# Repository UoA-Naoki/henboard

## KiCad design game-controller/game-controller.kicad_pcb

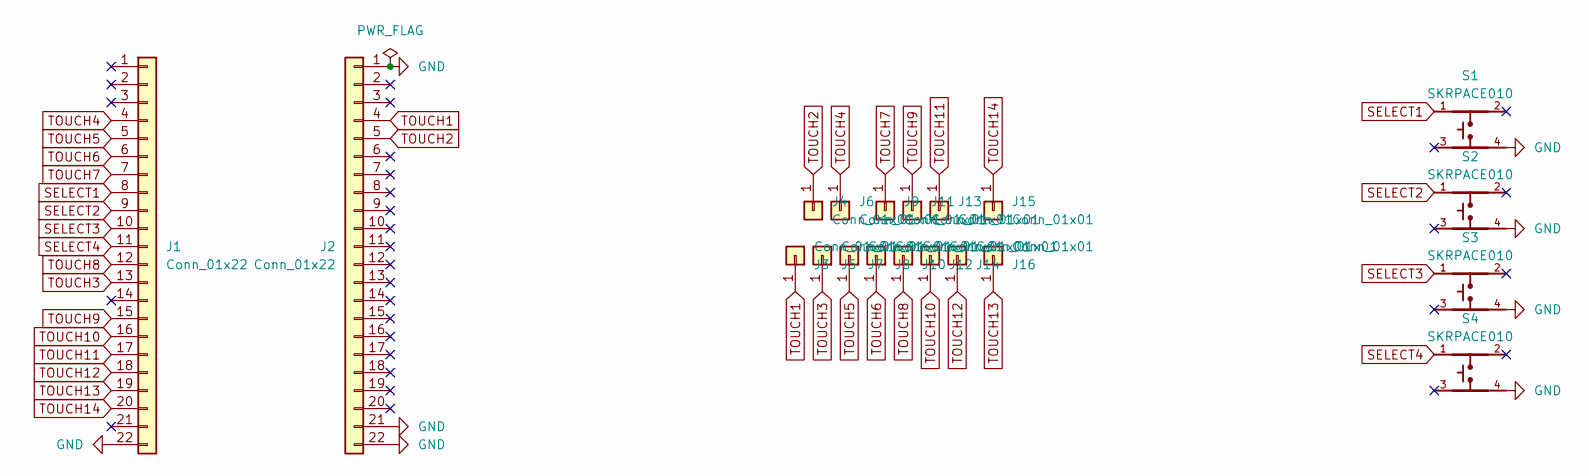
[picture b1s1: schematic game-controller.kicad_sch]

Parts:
J1, J2: Conn_01x22; PinHeader_1x22_P2.54mm_Vertical
J3, J4, J5, J6, J7, J8, J9, J10, J11, J12, J13, J14, J15, J16: Conn_01x01; Pad-CapacitiveTouch
S1, S2, S3, S4: SKRPACE010

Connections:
GND: J1.22, J2.1, J2.21, J2.22, S1.4, S2.4, S3.4, S4.4
SELECT1: J1.8, S1.1
SELECT2: J1.9, S2.1
SELECT3: J1.10, S3.1
SELECT4: J1.11, S4.1
TOUCH1: J2.4, J3.1
TOUCH2: J2.5, J4.1
TOUCH3: J1.13, J5.1
TOUCH4: J1.4, J6.1
TOUCH5: J1.5, J7.1
TOUCH6: J1.6, J8.1
TOUCH7: J1.7, J9.1
TOUCH8: J1.12, J10.1
TOUCH9: J1.15, J11.1
TOUCH10: J1.16, J12.1
TOUCH11: J1.17, J13.1
TOUCH12: J1.18, J14.1
TOUCH13: J1.19, J16.1
TOUCH14: J1.20, J15.1

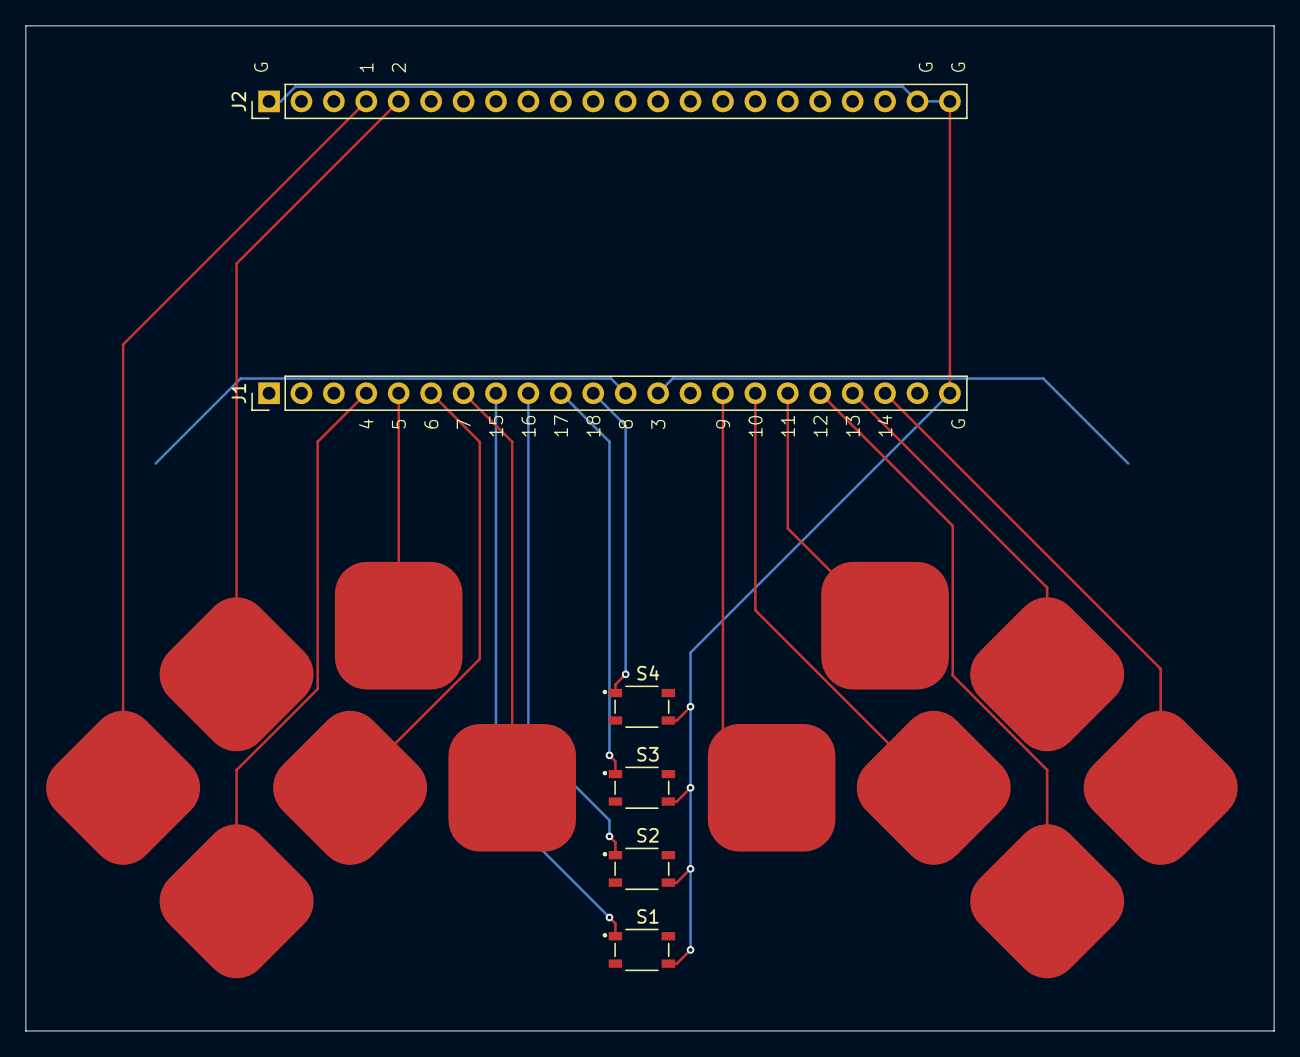
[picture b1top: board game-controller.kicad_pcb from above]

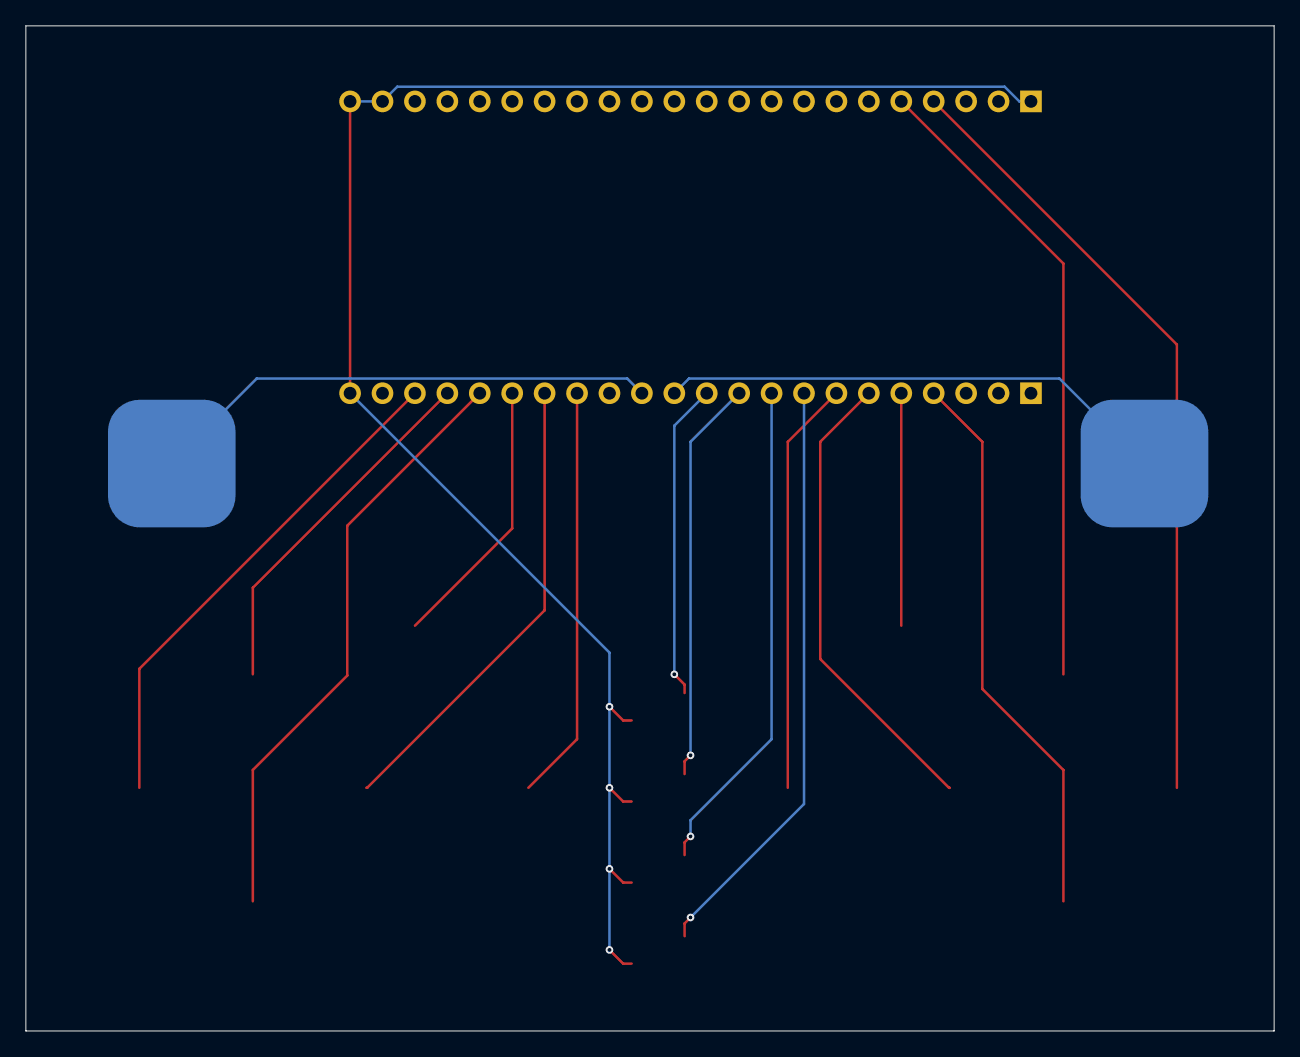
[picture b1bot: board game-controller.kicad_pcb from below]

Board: 2 copper layers, 97.8 x 78.7 mm, 20 parts (2 on the bottom side), 19 nets.

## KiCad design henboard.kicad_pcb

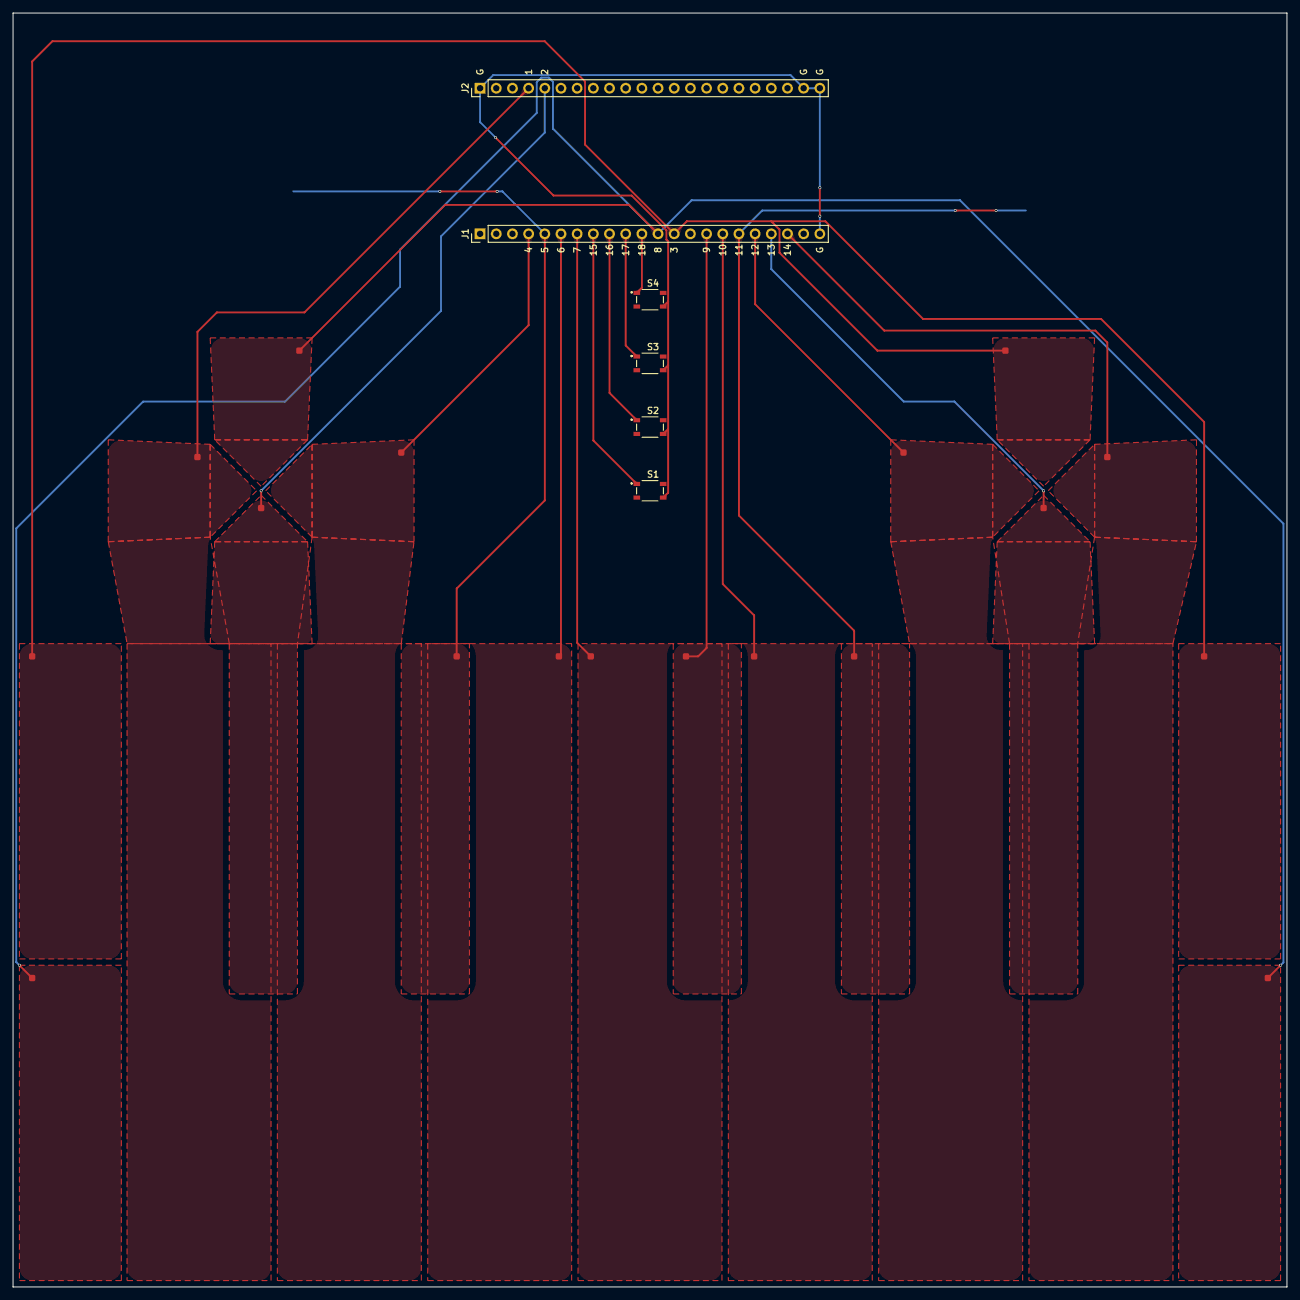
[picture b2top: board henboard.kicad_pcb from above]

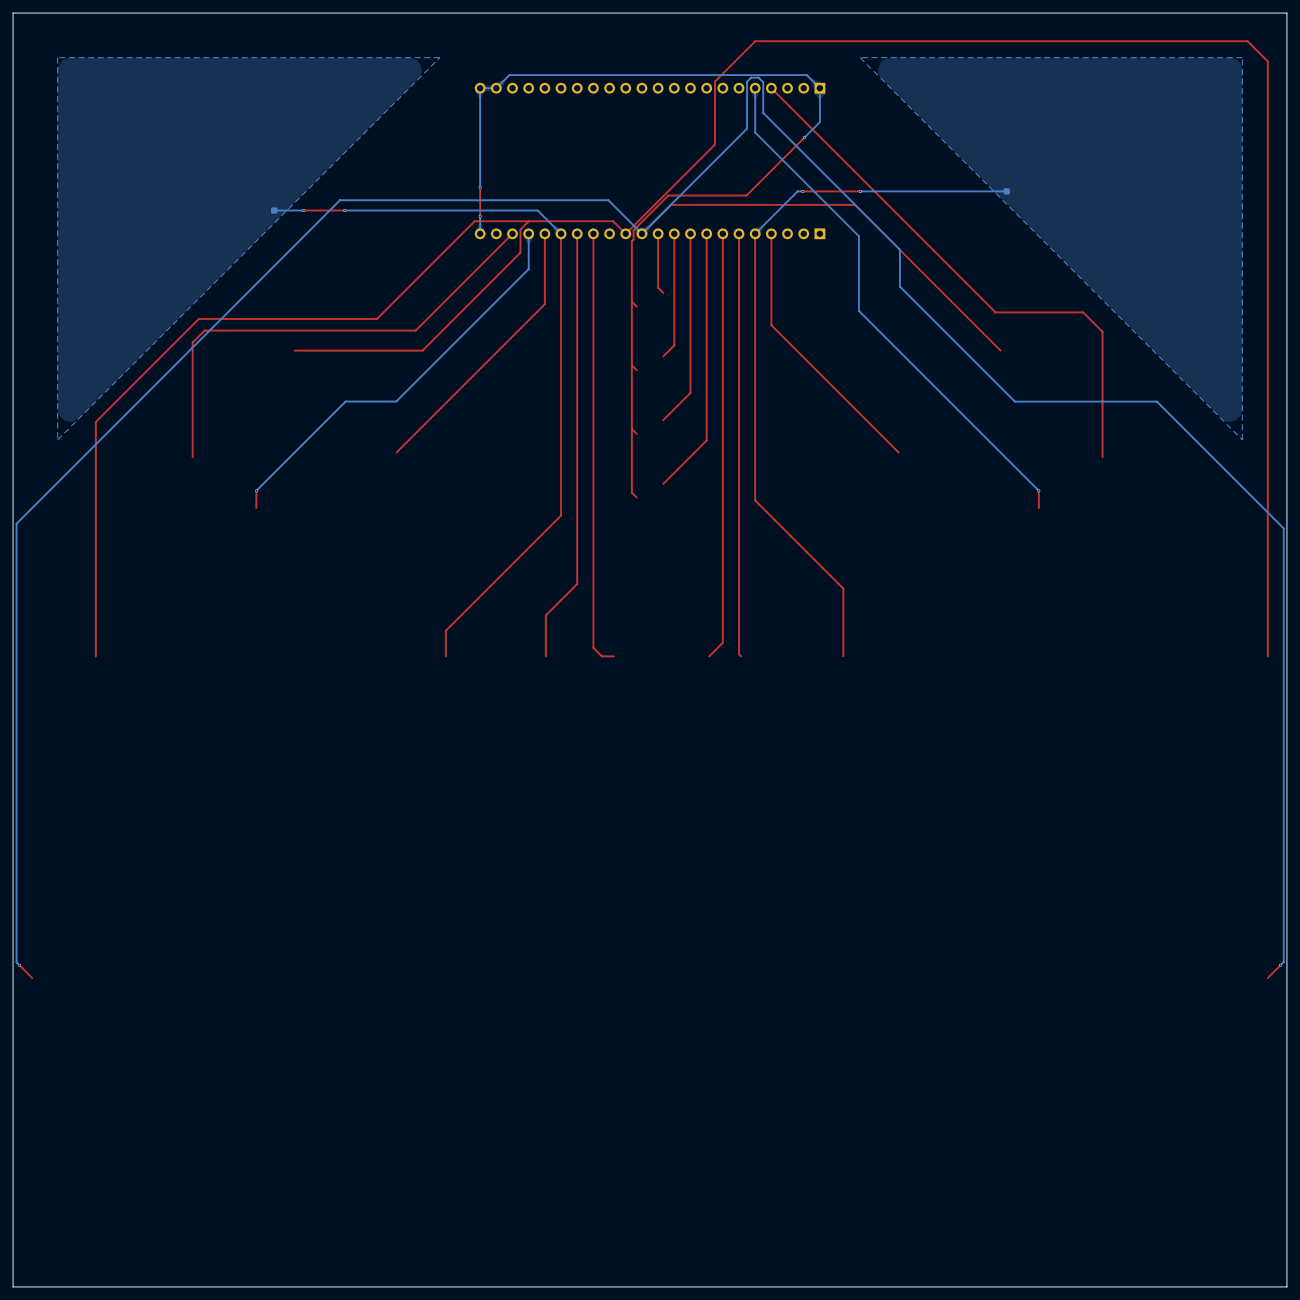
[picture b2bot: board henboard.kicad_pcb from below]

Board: 2 copper layers, 200.0 x 200.0 mm, 26 parts (2 on the bottom side), 19 nets.

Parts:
J1, J2: Conn_01x22; PinHeader_1x22_P2.54mm_Vertical
J3, J4, J5, J6, J7, J8, J9, J10, J11, J12, J13, J14, J15, J16, J17, J18, J19, J20, J21, J22: Conn_01x01; Pad-CapacitiveTouch-small
S1, S2, S3, S4: SKRPACE010

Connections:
GND: J1.22, J2.1, J2.21, J2.22, S1.4, S2.4, S3.4, S4.4
SELECT1: J1.8, S1.1
SELECT2: J1.9, S2.1
SELECT3: J1.10, S3.1
SELECT4: J1.11, S4.1
TOUCH1: J2.4, J5.1
TOUCH2: J2.5, J6.1
TOUCH3: J1.13, J3.1, J18.1, J21.1
TOUCH4: J1.4, J7.1
TOUCH5: J1.5, J9.1, J10.1
TOUCH6: J1.6, J11.1
TOUCH7: J1.7, J12.1
TOUCH8: J1.12, J4.1, J8.1, J22.1
TOUCH9: J1.15, J13.1
TOUCH10: J1.16, J14.1
TOUCH11: J1.17, J15.1, J16.1
TOUCH12: J1.18, J17.1
TOUCH13: J1.19, J19.1
TOUCH14: J1.20, J20.1

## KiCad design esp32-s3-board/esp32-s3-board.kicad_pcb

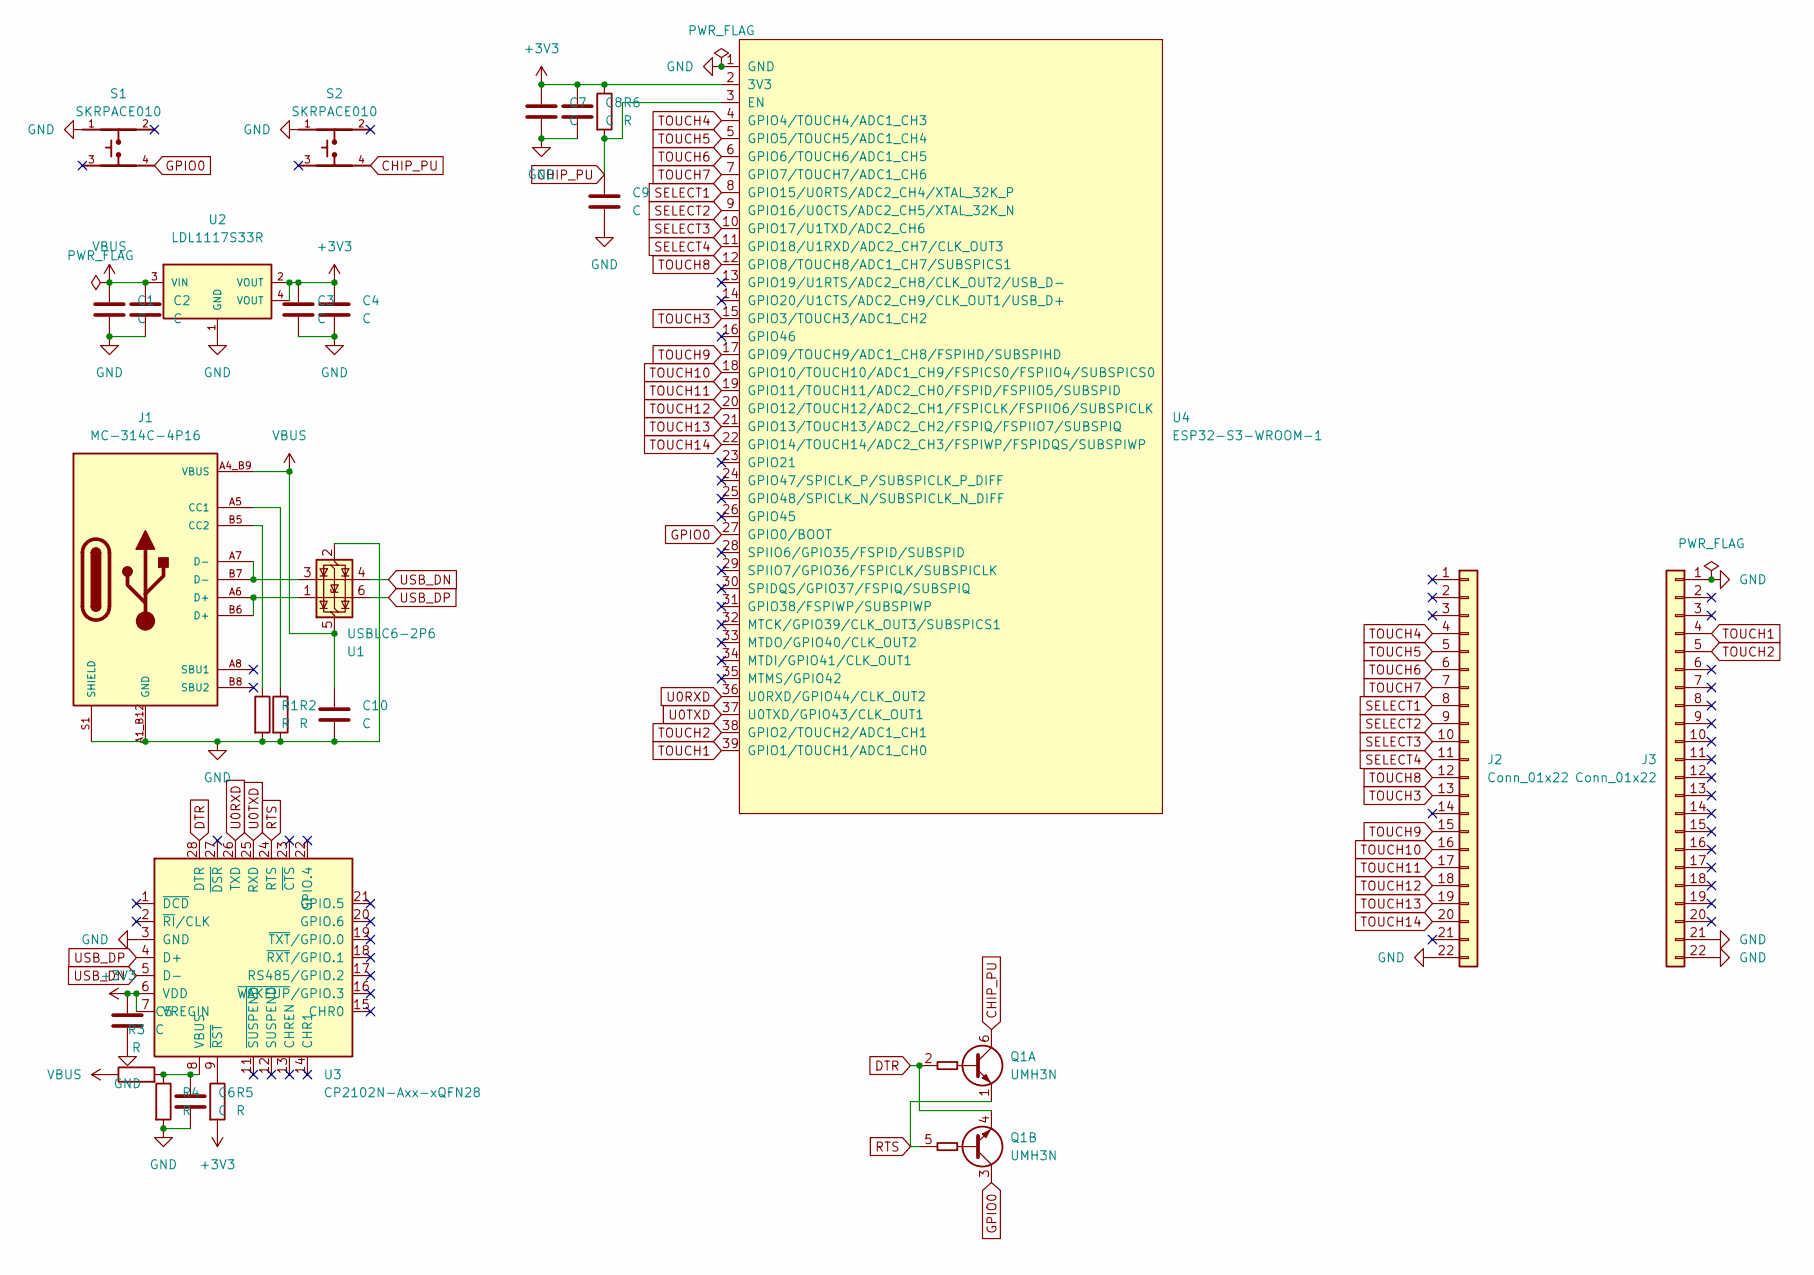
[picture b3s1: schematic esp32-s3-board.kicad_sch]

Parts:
C1, C2, C3, C4, C5, C6, C7, C8, C9, C10: C; C_0603_1608Metric_Pad1.08x0.95mm_HandSolder
J1: MC-314C-4P16; USB-C-SMD_MC-314C-4P16
J2, J3: Conn_01x22; PinHeader_1x22_P2.54mm_Vertical
Q1: UMH3N; SOT-363_SC-70-6
R1, R2, R3, R4, R5, R6: R; R_0603_1608Metric_Pad0.98x0.95mm_HandSolder
S1, S2: SKRPACE010
U1: USBLC6-2P6; SOT-666
U2: LDL1117S33R
U3: CP2102N-Axx-xQFN28; QFN-28-1EP_5x5mm_P0.5mm_EP3.35x3.35mm
U4: ESP32-S3-WROOM-1

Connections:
+3V3: C3.1, C4.1, C5.1, C7.1, C8.1, R5.2, R6.1, U2.2 (VOUT), U2.4 (VOUT), U3.6 (VDD), U3.7 (VREGIN), U4.2 (3V3)
CHIP_PU: C9.1, Q1.6 (C1), R6.2, S2.4, U4.3 (EN)
DTR: Q1.2 (B1), Q1.4 (E2), U3.28 (DTR)
GND: C1.2, C2.2, C3.2, C4.2, C5.2, C6.1, C7.2, C8.2, C9.2, C10.1, J1.A1_B12 (GND), J1.B1_A12 (GND), J1.S1 (SHIELD), J1.S2 (SHIELD), J1.S3 (SHIELD), J1.S4 (SHIELD), J2.22, J3.1, J3.21, J3.22, R1.2, R2.2, R4.2, S1.1, S2.1, U1.2 (GND), U2.1 (GND), U3.3 (GND), U3.29 (GND), U4.1 (GND), U4.40 (GND), U4.41 (GND)
GPIO0: Q1.3 (C2), S1.4, U4.27 (GPIO0/BOOT)
unnamed: J1.A5 (CC1), R2.1
unnamed: J1.B5 (CC2), R1.1
unnamed: J1.A6 (D+), J1.B6 (D+), U1.1 (I/O1)
unnamed: J1.A7 (D-), J1.B7 (D-), U1.3 (I/O2)
unnamed: C6.2, R3.2, R4.1, U3.8 (VBUS)
unnamed: R5.1, U3.9 (~RST)
RTS: Q1.1 (E1), Q1.5 (B2), U3.24 (RTS)
SELECT1: J2.8, U4.8 (GPIO15/U0RTS/ADC2_CH4/XTAL_32K_P)
SELECT2: J2.9, U4.9 (GPIO16/U0CTS/ADC2_CH5/XTAL_32K_N)
SELECT3: J2.10, U4.10 (GPIO17/U1TXD/ADC2_CH6)
SELECT4: J2.11, U4.11 (GPIO18/U1RXD/ADC2_CH7/CLK_OUT3)
TOUCH1: J3.4, U4.39 (GPIO1/TOUCH1/ADC1_CH0)
TOUCH2: J3.5, U4.38 (GPIO2/TOUCH2/ADC1_CH1)
TOUCH3: J2.13, U4.15 (GPIO3/TOUCH3/ADC1_CH2)
TOUCH4: J2.4, U4.4 (GPIO4/TOUCH4/ADC1_CH3)
TOUCH5: J2.5, U4.5 (GPIO5/TOUCH5/ADC1_CH4)
TOUCH6: J2.6, U4.6 (GPIO6/TOUCH6/ADC1_CH5)
TOUCH7: J2.7, U4.7 (GPIO7/TOUCH7/ADC1_CH6)
TOUCH8: J2.12, U4.12 (GPIO8/TOUCH8/ADC1_CH7/SUBSPICS1)
TOUCH9: J2.15, U4.17 (GPIO9/TOUCH9/ADC1_CH8/FSPIHD/SUBSPIHD)
TOUCH10: J2.16, U4.18 (GPIO10/TOUCH10/ADC1_CH9/FSPICS0/FSPIIO4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)
TOUCH11: J2.17, U4.19 (GPIO11/TOUCH11/ADC2_CH0/FSPID/FSPIIO5/S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)
TOUCH12: J2.18, U4.20 (GPIO12/TOUCH12/ADC2_CH1/FSPICLK/FSPIIO6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)
TOUCH13: J2.19, U4.21 (GPIO13/TOUCH13/ADC2_CH2/FSPIQ/FSPIIO7/S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)
TOUCH14: J2.20, U4.22 (GPIO14/TOUCH14/ADC2_CH3/FSPIWP/FSPIDQS/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)
U0RXD: U3.26 (TXD), U4.36 (U0RXD/GPIO44/CLK_OUT2)
U0TXD: U3.25 (RXD), U4.37 (U0TXD/GPIO43/CLK_OUT1)
USB_DN: U1.4 (I/O2), U3.5 (D-)
USB_DP: U1.6 (I/O1), U3.4 (D+)
VBUS: C1.1, C2.1, C10.2, J1.A4_B9 (VBUS), J1.B4_A9 (VBUS), R3.1, U1.5 (VBUS), U2.3 (VIN)

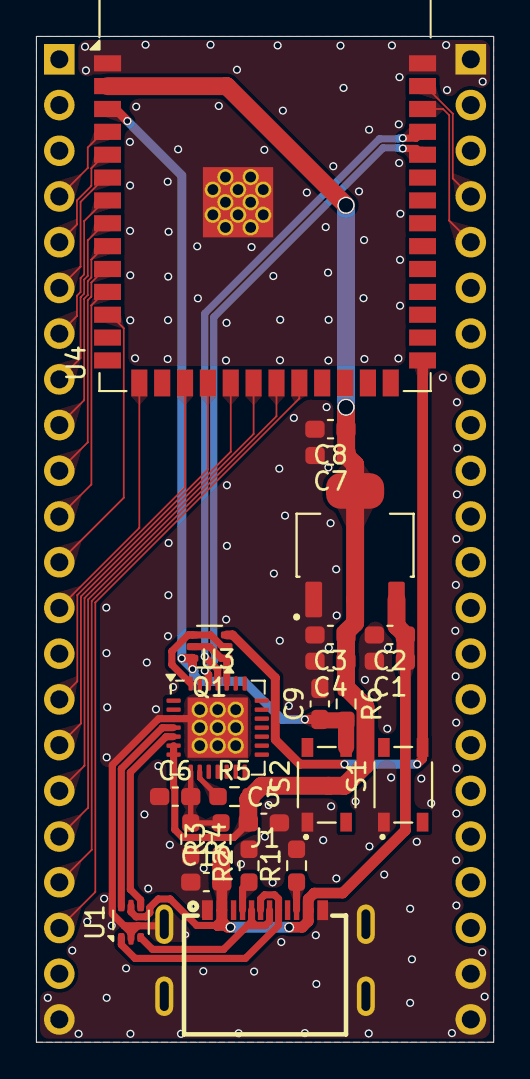
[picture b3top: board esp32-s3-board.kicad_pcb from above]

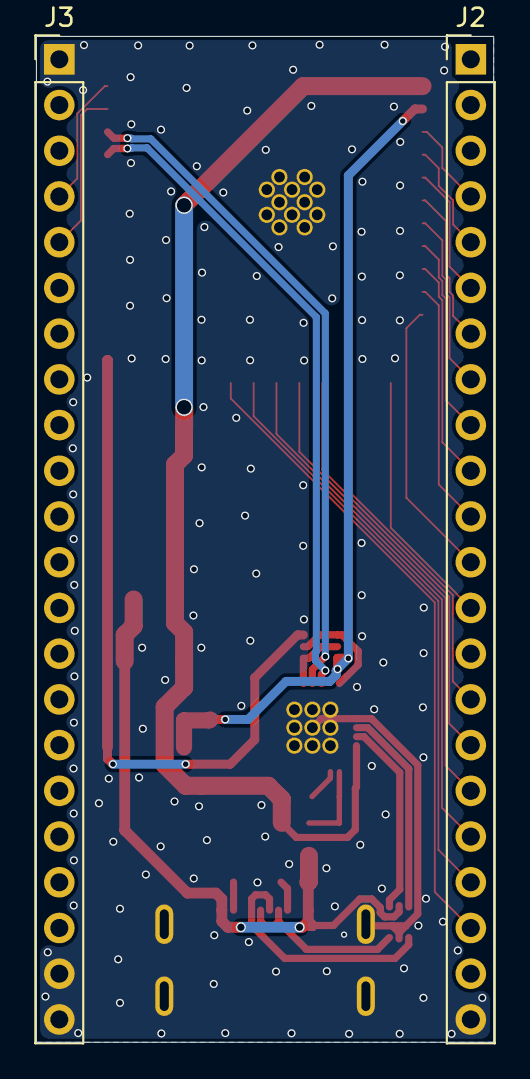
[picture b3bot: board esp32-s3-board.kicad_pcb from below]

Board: 2 copper layers, 25.4 x 55.9 mm, 26 parts (2 on the bottom side), 35 nets.

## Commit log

2025-05-16 module -> esp32-s3-board
2025-05-16 add SKRPACE010 library
2025-05-16 add SKRPACE010 library to digital-piano
2025-05-16 add libraries to henboard
2025-05-16 update library of PWR_FLAG, EARTH -> GND
2025-05-16 update SKRPACE010 symbols in digital-piano schematic
2025-05-16 ignore *.lck
2025-05-20 Assign footprints to henboard
2025-05-20 Add Pad-CapacitiveTouch library to digital-piano
2025-05-20 Assign footprints to digital-piano
2025-05-21 Add symbol and footprints libraries to game-controller
2025-05-21 Add symbol and footprints libraries to keyboard
2025-05-21 Change the name of the footprint library of touchpad
2025-05-21 Add symbol and footprints libraries to touchpad
2025-05-21 Add symbols and footprints libraries to esp32-s3-board
2025-06-10 Complete keyboard
2025-06-10 Complete game-controller
2025-06-10 Add silk for ESP32-S3-Devkit-C1
2025-06-12 Fix position of touch pads
2025-06-12 Complete digital-piano
2025-06-14 Add symbols, footprints and 3d model libraries to esp32-s3-board
2025-06-14 Modify LDL111S33R's footprint
2025-06-14 Complete esp32-s3-board
2025-06-14 Fix touch position mistakes
2025-06-14 Add Silkscreen to be able to identify board direction
2025-06-14 Remove unnecessary changes
2025-06-14 Modify Pad-CapacitiveTouch library
2025-06-14 Apply library changes to digital-piano
2025-06-14 Apply library changes to game-controller
2025-06-14 Apply Pad-CapacitiveTouch libary modification to keyboard
2025-06-14 Change PCB size of game-controller because of fablication price
2025-06-14 Make vias bigger and add teardrop
2025-06-14 Change schematic
2025-06-14 Add footprints libraries to henboard
2025-06-14 Change PCB size of piano because of fablication price
2025-06-14 Fix warning
2025-06-14 Fix Pad-CapacitiveTouch footprint and apply to boards
2025-06-14 Add specific values to schematic
2025-06-14 Add footprint to henboard
2025-06-14 Fix capacitor values
2025-06-14 Change schematic annotation and footprint assignments
2025-06-15 Finish schematic
2025-06-15 Finish piano
2025-06-15 Finish all
2025-06-15 Thicken silk letters
2025-06-19 Add firmware and driver
2025-06-20 Fix sending too many packets
2025-06-20 Change key layout and threshold
2025-06-20 Make LSB to the right and thresholds refer pin number
2025-06-20 Send ascii and check by driver
2025-06-20 Change send timing. Send when released
2025-06-20 add MIDI_piano.ino
2025-06-20 add digital-piano-firmware
2025-06-21 Support more characters
2025-07-01 Change threshold value
